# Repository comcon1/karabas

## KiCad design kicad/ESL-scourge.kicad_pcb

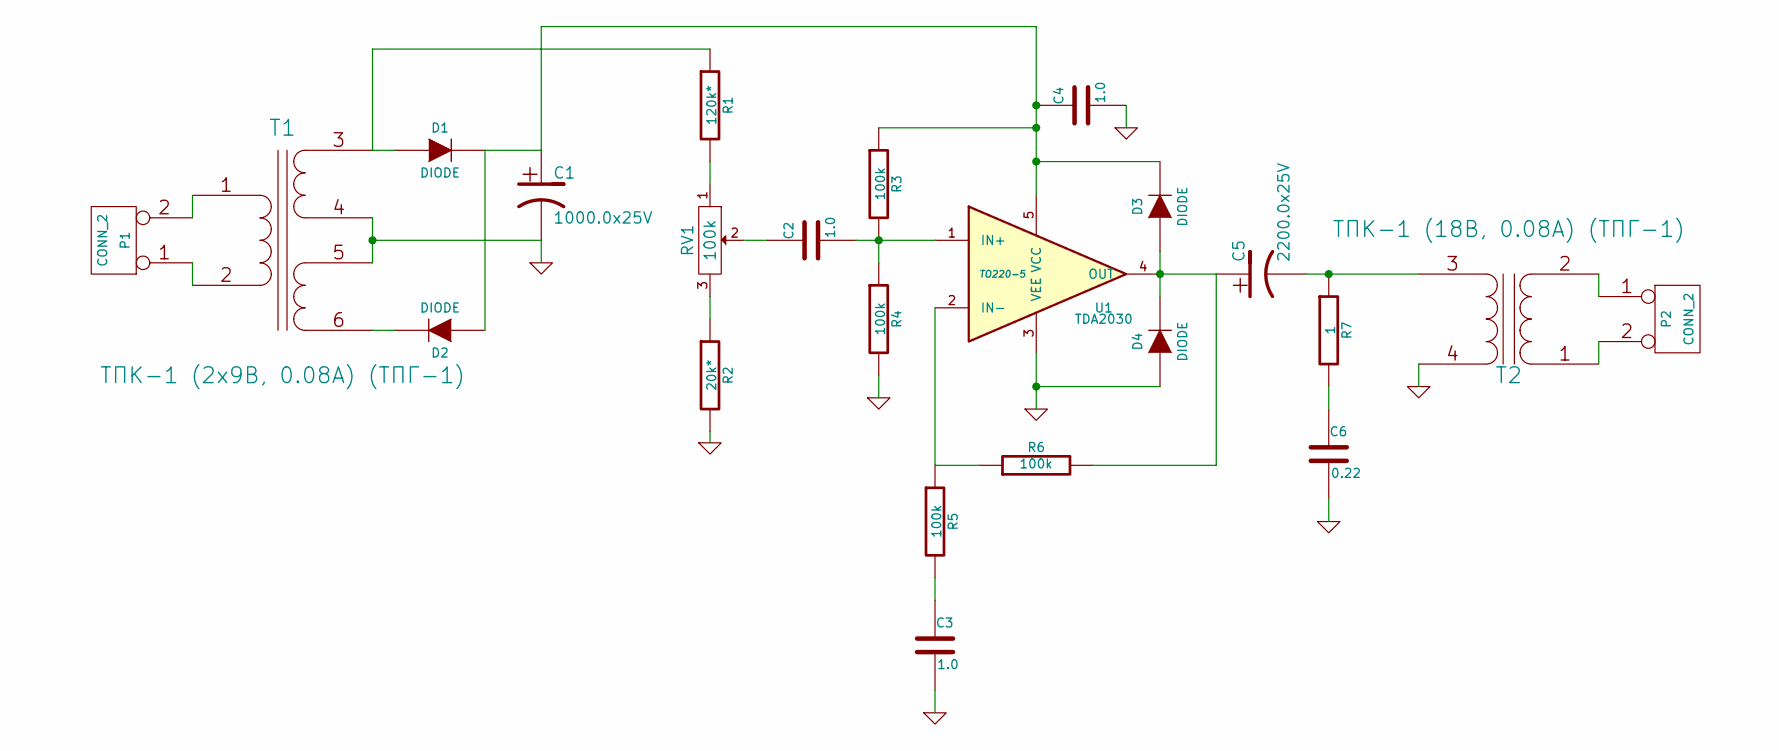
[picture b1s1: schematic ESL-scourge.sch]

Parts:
C1: 1000.0x25V
C2, C3, C4: 1.0
C5: 2200.0x25V
C6: 0.22
D1, D2, D3, D4: DIODE
P1, P2: CONN_2
R1: 120k*
R2: 20k*
R3, R4, R5, R6: 100k
R7: 1
RV1: 100k
T1: ТПК-1 (2х9В, 0.08А) (ТПГ-1)
T2: ТПК-1 (18В, 0.08А) (ТПГ-1)
U1: TDA2030; TO220-5

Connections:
GND: C1.2, C3.2, C4.2, C6.2, D4.1 (A), R2.2, R4.2, T1.4 (SB), T1.5 (SC), T2.4 (SB), U1.3 (VEE)
unnamed: P2.1, T2.2 (AB)
unnamed: P2.2 (PM), T2.1 (AA)
unnamed: D2.2 (K), T1.6 (SD)
unnamed: P1.1, T1.2 (AB)
unnamed: P1.2 (PM), T1.1 (AA)
unnamed: R1.2, RV1.1
unnamed: D1.1 (A), R1.1, T1.3 (SA)
unnamed: R2.1, RV1.3
unnamed: C2.1, RV1.2
unnamed: C3.1, R5.2
unnamed: C6.1, R7.2
unnamed: C5.1, D3.1 (A), D4.2 (K), R6.2, U1.4 (OUT)
unnamed: C5.2, R7.1, T2.3 (SA)
unnamed: R5.1, R6.1, U1.2 (IN-)
unnamed: C1.1, C4.1, D1.2 (K), D2.1 (A), D3.2 (K), R3.1, U1.5 (VCC)
unnamed: C2.2, R3.2, R4.1, U1.1 (IN+)

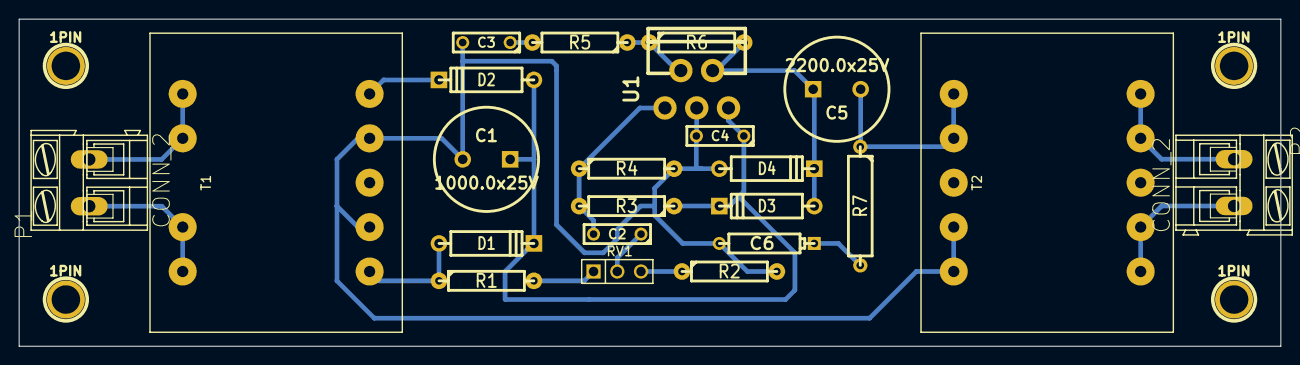
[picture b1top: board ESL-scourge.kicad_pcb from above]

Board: 2 copper layers, 135.0 x 35.0 mm, 27 parts (0 on the bottom side), 17 nets.

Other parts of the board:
1PIN, 1PIN#2, 1PIN#3, 1PIN#4: P***; 1pin

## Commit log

2016-02-22 main descriptor
2016-02-22 Major version made by kuzya at 21/02/16
2016-02-22 Awaiting for subj
2016-02-23 Bug in pcb fixed
2016-02-23 Silks layer corrected
2016-04-01 Comments for debugging added
2016-04-02 Critical bug fixed in power supply circuit - wrong diode polarity
2016-04-04 corpus - variant zero. Need for pcb to be redesigned. Transformator was changed but not comitted yet.
2016-04-06 fixed bugs of the first corpus
2016-04-11 Several critical bugs fixed - wrong diode polarity in output bridge, pullup resistors added in slon-control scheme
2016-05-02 component values corrected. Work in progress
2024-09-26 Add initial maket_lovat as a separate branch (kicad folder only)
